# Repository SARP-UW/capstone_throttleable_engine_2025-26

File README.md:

# capstone_throttleable_engine_2025-26

2025-2026 SARP Capstone Project — a throttleable ethanol / nitrous engine injector testbed.

This repository includes:
- **software** (`software/`) — Python DAQ, valve actuation, throttle control, and web GUI
- **hardware** (`hardware/`) — KiCAD PCB design for DAQ, valve actuation, and servo control
- **analysis** (`analysis/`) — Thermal, structural, and control system analysis 

---

## Software

**Package:** `deep-thrott-code` v0.1.0  
**Requires:** Python ≥ 3.10

### Installation

```bash
pip install -e .
```

### Running the GUI

The system is split into two servers:

| Server | Default address | Role |
|--------|----------------|------|
| **Backend** | `http://0.0.0.0:6001` | DAQ, valve control, F3C sequencer, Socket.IO |
| **GUI** | `http://127.0.0.1:5000` | Serves the web frontend only |

When you open the GUI in a browser, the frontend JS automatically connects to the backend via Socket.IO on port 6001 (same host, different port). The backend streams live sensor data at ~10 Hz and receives commands (valve actuation, sequence control, start/stop logging) from the GUI.

**Running both on the same machine:**

```bash
# Terminal 1 — start the backend
python -m deep_thrott_code.main --host 0.0.0.0 --port 6001

# Terminal 2 — start the GUI server
python -m deep_thrott_code.gui.run_gui --host 0.0.0.0 --port 5000
```

Once the server is running, open any browser on the same network and navigate to:

```
http://<host-ip>:5000
```

If running locally, just go to `http://localhost:5000` or `http://127.0.0.1:5000`.  
If running on a Raspberry Pi, use the Pi's IP address: `http://192.168.x.x:5000`.

**Running backend on a Pi, GUI on your laptop:**

```bash
# On the Pi
python -m deep_thrott_code.main --host 0.0.0.0 --port 6001

# On your laptop (point GUI at the Pi's IP)
python -m deep_thrott_code.gui --backend http://192.168.x.x:6001 --host 127.0.0.1 --port 5000
```

Then open `http://localhost:5000` on your laptop.

**What you see in the browser:**

The GUI is a single-page app with:
- **Line control tabs** — PID diagrams with live valve state and pressure readouts for ethanol and nitrous lines
- **DAQ tabs** — 18 real-time sensor plots (auto-scaled, 300-point history)
- **Sequence panel** — step-by-step fire sequence tracking with manual step execution
- **Settings** — simulation toggle, test selection (hotfire / cold flow), sensor selection, theme

**CLI flags (main backend):**

| Flag | Description |
|------|-------------|
| `--host` | Bind host (default `0.0.0.0`) |
| `--port` | Bind port (default `6001`) |
| `--simulation` | Run without hardware (sensor simulation) |
| `--no-gui-server` | Start backend only, no Flask server |
| `--autostart` | Automatically start DAQ on launch |
| `--no-sequencer` | Disable the F3C fire sequencer |
| `--debug` | Enable Flask debug mode |

### Structure

```
software/src/deep_thrott_code/
├── main.py               # Entry point
├── backend/              # App factory, GUI command handlers, DAQ runtime
├── gui/                  # Flask + Socket.IO web interface (routes, sockets)
├── daq/                  # Data acquisition — ADC drivers and sensor interfaces
├── f3c/                  # Sequencer and valve control
├── control/              # PID throttle controller and servo characterization
└── config/               # Default configuration files
```

**Utility scripts** (`software/scripts/`):
- `hotfire.py` — Hotfire sequence runner
- `calibrate_sensors.py` — Sensor calibration
- `plot_daq_csv.py` — Plot data from DAQ CSV logs
- `adc_smoke_test.py` — ADC hardware smoke test

### Dependencies

| Package | Purpose |
|---------|---------|
| Flask, Flask-SocketIO | Web GUI server |
| NumPy, SciPy | Numerical computation |
| PyYAML | Configuration parsing |
| PySerial | Serial communication |
| Matplotlib | Data visualization |
| RPi.GPIO, pigpio, spidev | GPIO and SPI (Linux/RPi only) |
| eventlet *(optional)* | Async server mode |

---

## Hardware

KiCAD project located in `hardware/cda-pcb/`. Includes schematic, PCB layout, Gerber files, and custom symbols/footprints.

---

## Analysis

- `analysis/control_dev/` — Control system models (MATLAB and Python)
- `analysis/engine_dev/` — Structural analysis (Python, based on GRACE methodology)

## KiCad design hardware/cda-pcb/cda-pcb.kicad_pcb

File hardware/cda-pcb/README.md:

# High-Precision Raspberry Pi DAQ Board

A custom Data Acquisition (DAQ) hat designed for the Raspberry Pi. This board interfaces with industrial sensors (RTDs, Load Cells, Pressure Transducers) to log and display live data with high precision.

The system features a robust, low-noise power architecture that manages 24VDC input to power the sensors, the precision analog circuitry, and the Raspberry Pi itself. It utilizes dual 24-bit ADCs communicating over SPI for high-resolution signal digitization.

## Features

* **Multi-Sensor Interface:** Three 15-position D-sub connectors for attaching RTDs, Load Cells, and Pressure Transducers.
* **Input Protection:** Every signal line is protected by TVS diode arrays to guard against ESD and surge events.
* **High-Resolution Sampling:** Dual 24-bit ADCs transmit data via SPI to the Raspberry Pi.
* **Low-Noise Power Architecture:**
    * Accepts 24 VDC input.
    * On-board Buck converters for high-efficiency voltage step-down.
    * LDOs and precision voltage references ensure clean power rails for the ADCs and sensors.
    * High-current supply dedicated to the Raspberry Pi.
* **Compact Design:** PCB fits within a 10cm x 10cm footprint to minimize manufacturing costs.

### 3D Rendering

### Layout View

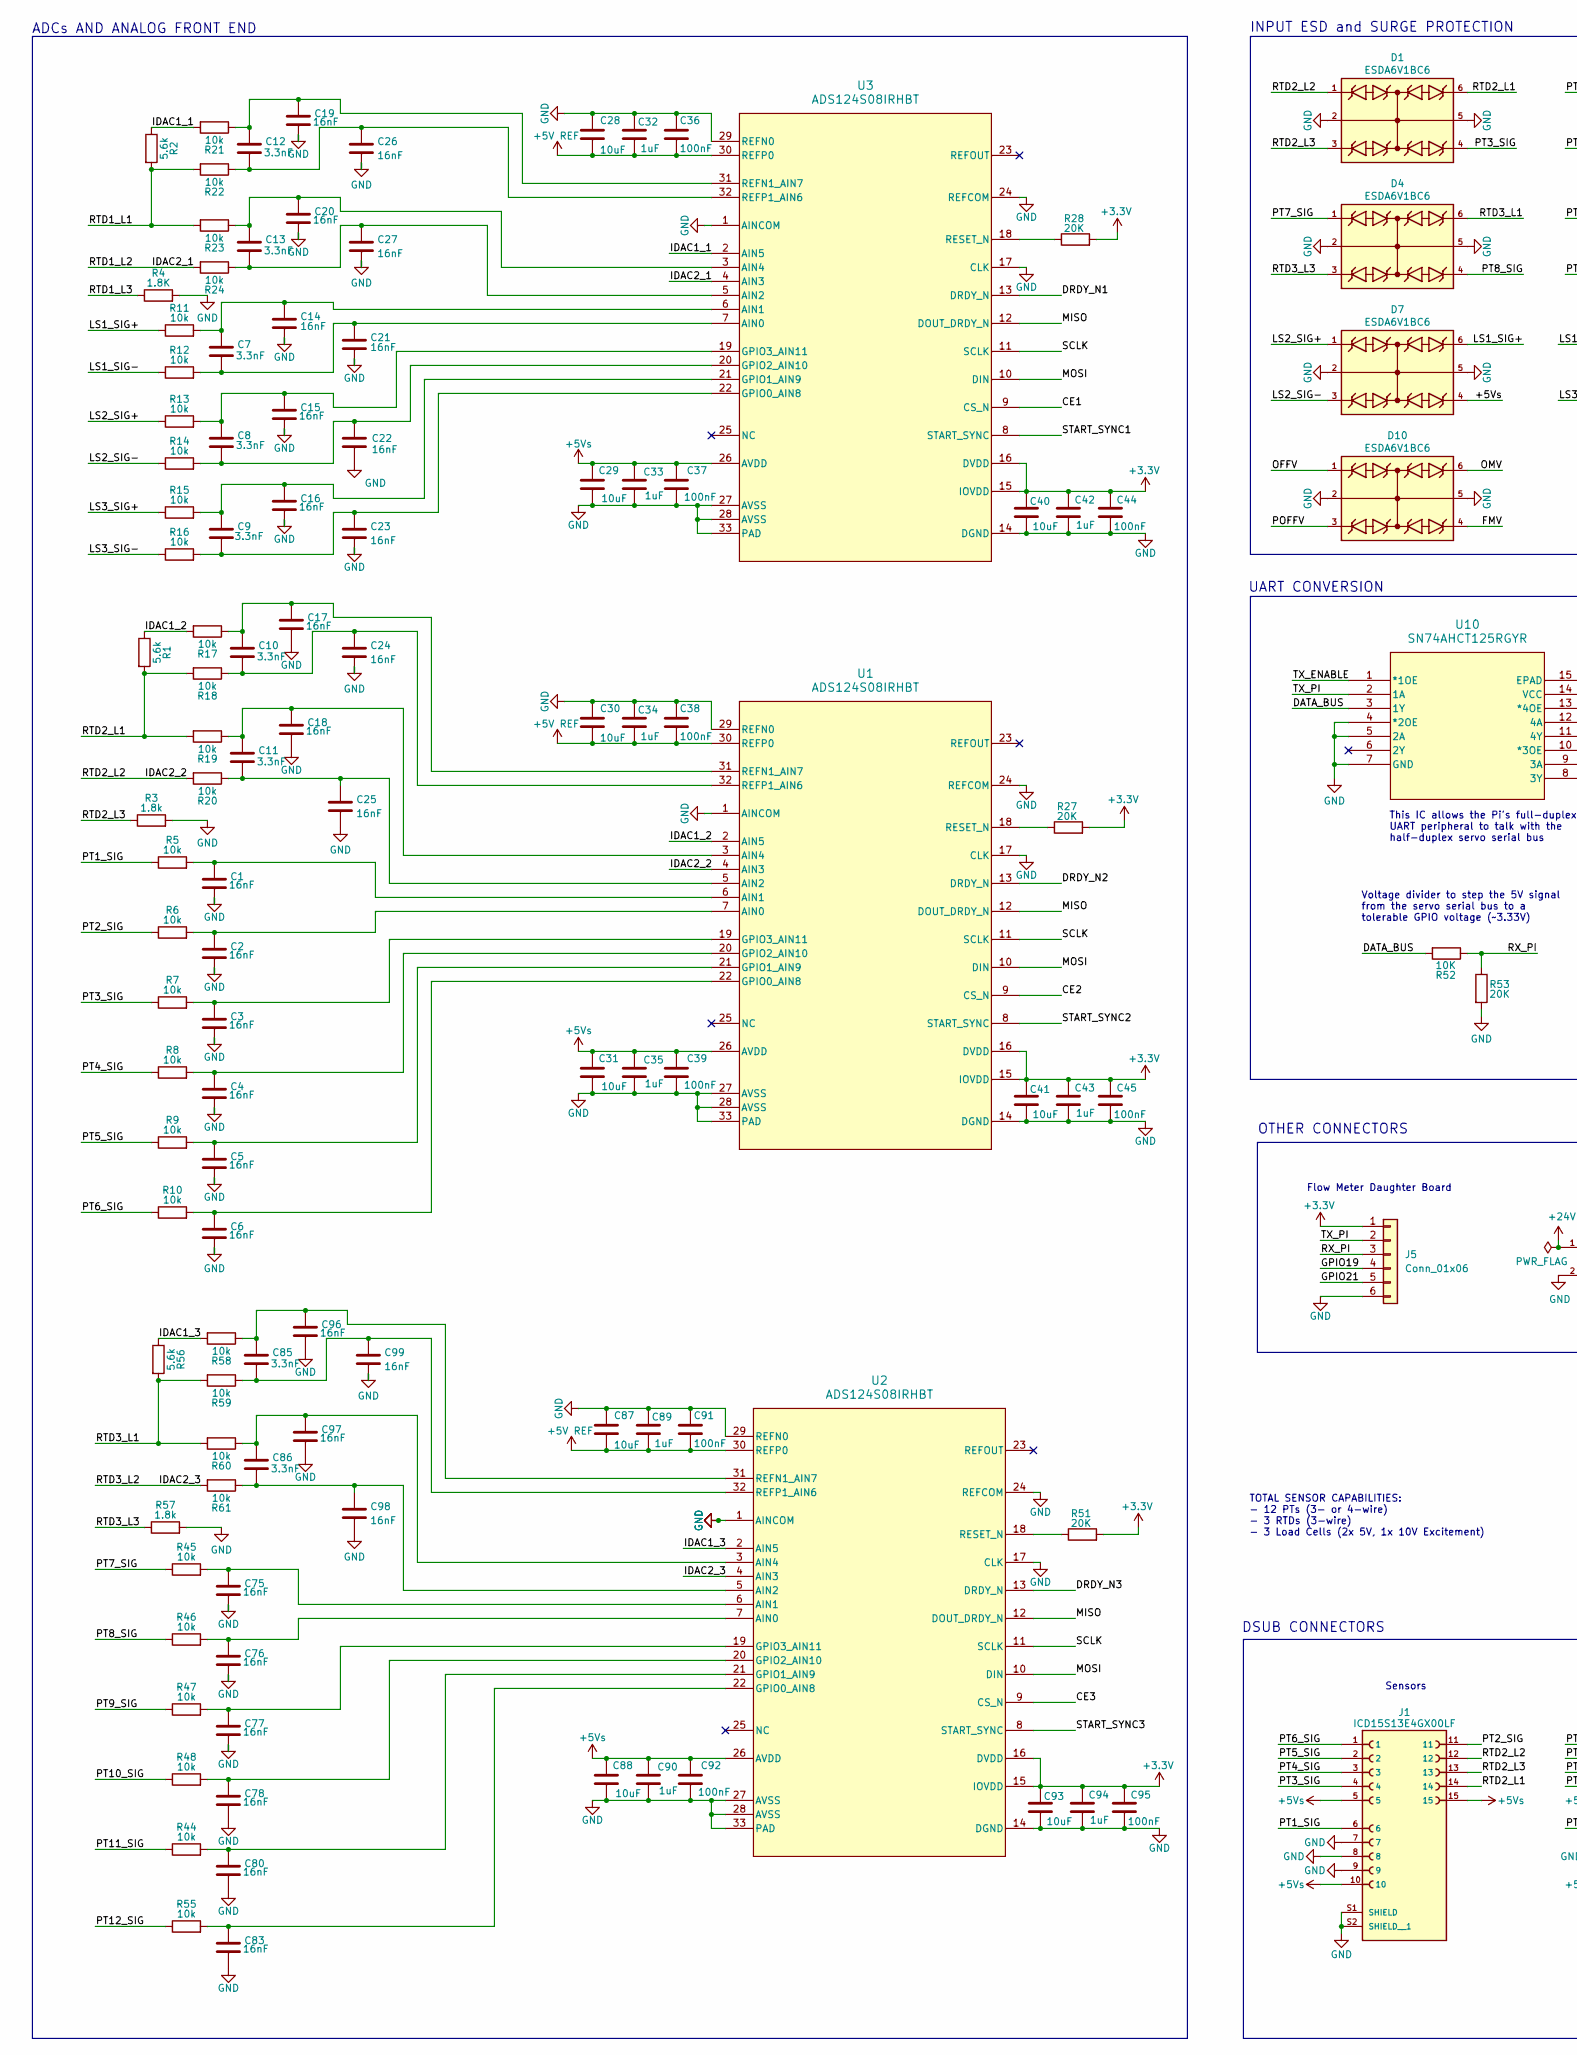
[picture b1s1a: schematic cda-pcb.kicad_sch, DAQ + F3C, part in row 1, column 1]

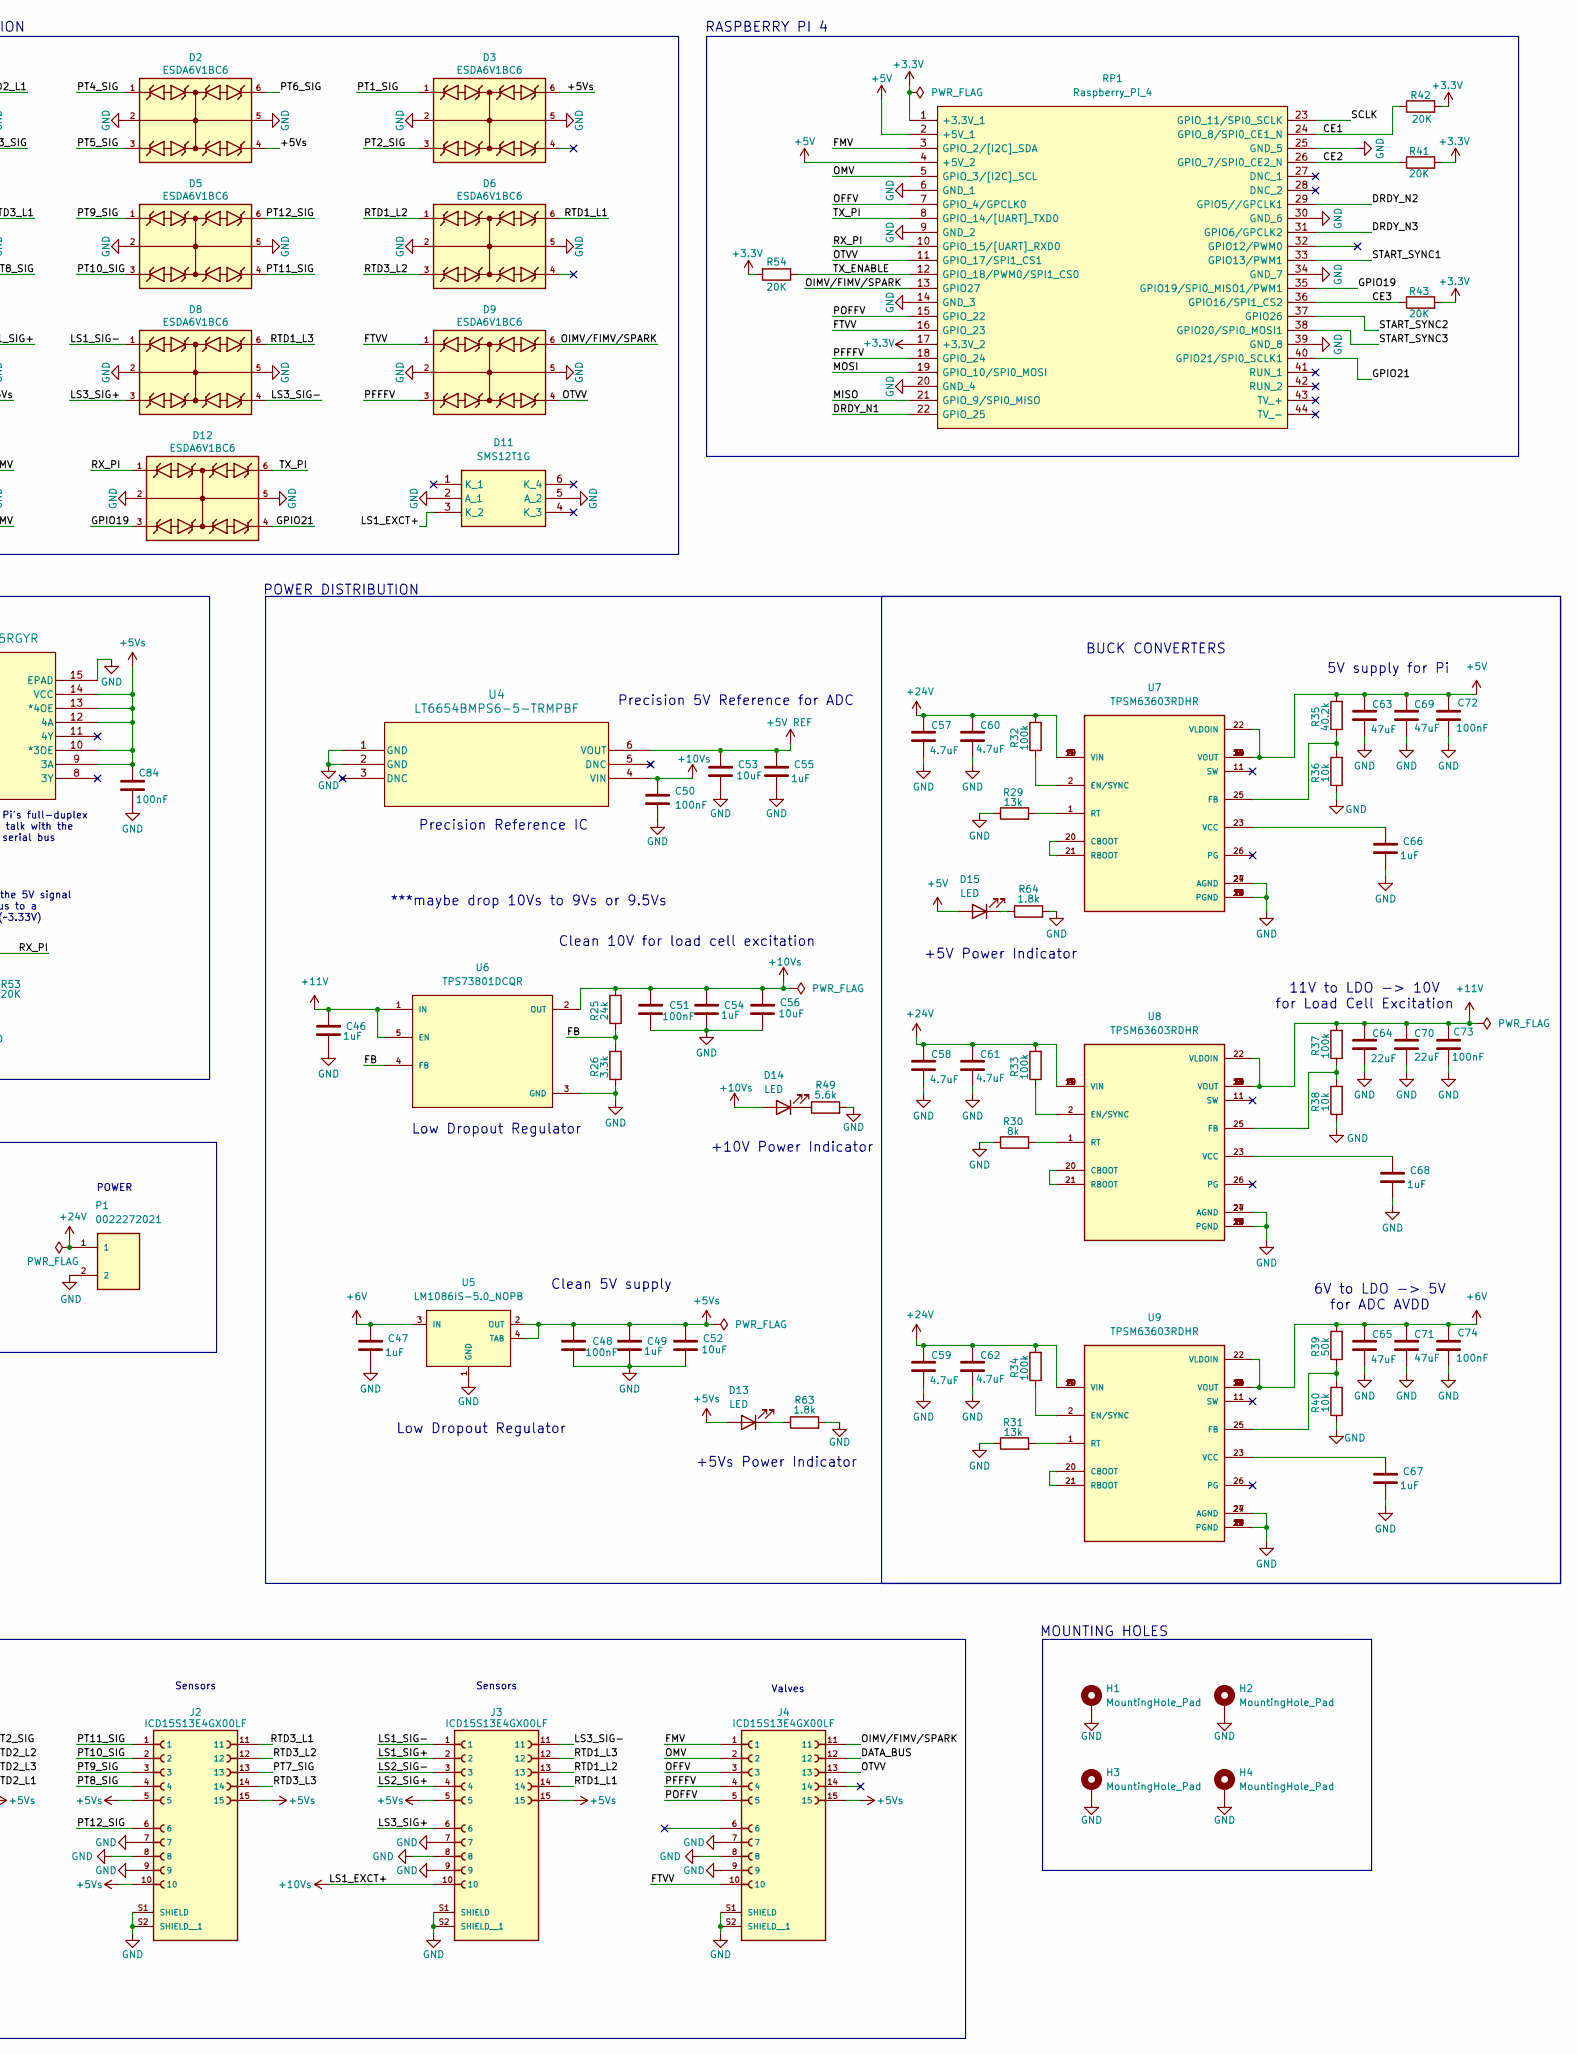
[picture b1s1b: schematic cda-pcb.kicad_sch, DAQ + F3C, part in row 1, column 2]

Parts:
C1, C2, C3, C4, C5, C6, C14, C15, C16, C17, C18, C19, C20, C21, C22, C23, C24, C25, C26, C27, C75, C76, C77, C78, C80, C83, C96, C97, C98, C99: 16nF; CAPC3216X95N
C7, C8, C9, C10, C11, C12, C13, C85, C86: 3.3nF; C_0603_1608Metric
C28, C29, C30, C31, C40, C41, C52, C53, C56, C87, C88, C93: 10uF; CAPC2012X145N
C32, C33, C34, C35, C42, C43, C46, C47, C49, C54, C55, C66, C67, C68, C89, C90, C94: 1uF; CAPC1608X94N
C36, C37, C38, C39, C44, C45, C48, C50, C51, C72, C73, C74, C84, C91, C92, C95: 100nF; CAPC1608X97N
C57, C58, C59, C60, C61, C62: 4.7uF; C_0805_2012Metric
C63, C65, C69, C71: 47uF; C_1206_3216Metric
C64, C70: 22uF; C_1206_3216Metric
D1, D2, D3, D4, D5, D6, D7, D8, D9, D10, D12: ESDA6V1BC6; SOT95P280X145-6N; PARTREV 2
D11: SMS12T1G; SOT95P275X110-6N; Manufacturer_Part_Number SMS12T1G; Mouser Part Number 863-SMS12T1G
D13, D14, D15: LED; LED_0805_2012Metric
H1, H2, H3, H4: MountingHole_Pad; MountingHole_2.5mm_Pad
J1, J2, J3, J4: ICD15S13E4GX00LF; AMPHENOL_ICD15S13E4GX00LF; PARTREV G
J5: Conn_01x06; PinHeader_1x06_P2.54mm_Vertical
P1: 0022272021; MOLEX_0022272021
R1, R2, R49, R56: 5.6k; R_0603_1608Metric
R3, R57, R63, R64: 1.8k; R_0603_1608Metric
R4: 1.8K; R_0603_1608Metric
R5, R6, R7, R8, R9, R10, R11, R12, R13, R14, R15, R16, R17, R18, R19, R20, R21, R22, R23, R24, R44, R45, R46, R47, R48, R55, R58, R59, R60, R61: 10k; R_0603_1608Metric
R25: 24k; RESC1508X50N
R26: 3.3k; RESC1508X50N
R27, R28, R41, R42, R43, R51, R53, R54: 20K; RESC1508X50N
R29, R31: 13k; RESC1508X50N
R30: 8k; RESC1508X50N
R32, R33, R34, R37: 100k; RESC1508X50N
R35: 40.2k; RESC1508X50N
R36, R38, R40: 10k; RESC1508X50N
R39: 50k; RESC1508X50N
R52: 10K; RESC1508X50N
RP1: Raspberry_Pi_4; raspberrypi_2_3; Manufacturer_Part_Number Raspberry Pi 2 or 3
U1, U2, U3: ADS124S08IRHBT; QFN50P500X500X100-33N
U4: LT6654BMPS6-5-TRMPBF; TSOT-23_S6_LIT
U5: LM1086IS-5.0_NOPB; TO254P1524X483-4N
U6: TPS73801DCQR; SOT127P706X180-6N
U7, U8, U9: TPSM63603RDHR; CONV_TPSM63602RDHR; PARTREV April 2022
U10: SN74AHCT125RGYR; RGY14_2P05X2P05

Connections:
+3.3V: C40.1, C41.1, C42.1, C43.1, C44.1, C45.1, C93.1, C94.1, C95.1, J5.1, R27.2, R28.2, R41.2, R42.2, R43.2, R51.2, R54.2, RP1.1 (+3.3V_1), RP1.17 (+3.3V_2), U1.15 (IOVDD), U1.16 (DVDD), U2.15 (IOVDD), U2.16 (DVDD), U3.15 (IOVDD), U3.16 (DVDD)
+5V: C63.2, C69.2, C72.1, D15.2 (A), R35.2, RP1.2 (+5V_1), RP1.4 (+5V_2), U7.7 (VOUT), U7.8 (VOUT), U7.9 (VOUT), U7.10 (VOUT), U7.12 (VOUT), U7.13 (VOUT), U7.14 (VOUT), U7.15 (VOUT), U7.22 (VLDOIN), U7.30 (VOUT)
+5V REF: C28.2, C30.2, C32.2, C34.2, C36.2, C38.2, C53.1, C55.1, C87.2, C89.2, C91.2, U1.30 (REFP0), U2.30 (REFP0), U3.30 (REFP0), U4.6 (VOUT)
+6V: C47.1, C65.2, C71.2, C74.1, R39.2, U5.3 (IN), U9.7 (VOUT), U9.8 (VOUT), U9.9 (VOUT), U9.10 (VOUT), U9.12 (VOUT), U9.13 (VOUT), U9.14 (VOUT), U9.15 (VOUT), U9.22 (VLDOIN), U9.30 (VOUT)
+11V: C46.1, C64.2, C70.2, C73.1, R37.2, U6.1 (IN), U6.5 (EN), U8.7 (VOUT), U8.8 (VOUT), U8.9 (VOUT), U8.10 (VOUT), U8.12 (VOUT), U8.13 (VOUT), U8.14 (VOUT), U8.15 (VOUT), U8.22 (VLDOIN), U8.30 (VOUT)
+24V: C57.2, C58.2, C59.2, C60.2, C61.2, C62.2, P1.1, R32.2, R33.2, R34.2, U7.3 (VIN), U7.4 (VIN), U7.18 (VIN), U7.19 (VIN), U8.3 (VIN), U8.4 (VIN), U8.18 (VIN), U8.19 (VIN), U9.3 (VIN), U9.4 (VIN), U9.18 (VIN), U9.19 (VIN)
/CE1: R42.1, RP1.24 (GPIO_8/SPI0_CE1_N), U3.9 (CS_N)
/CE2: R41.1, RP1.26 (GPIO_7/SPI0_CE2_N), U1.9 (CS_N)
/CE3: R43.1, RP1.36 (GPIO16/SPI1_CS2), U2.9 (CS_N)
/DATA_BUS: J4.12, R52.2, U10.3 (1Y)
/DRDY_N1: RP1.22 (GPIO_25), U3.13 (DRDY_N)
/DRDY_N2: RP1.29 (GPIO5//GPCLK1), U1.13 (DRDY_N)
/DRDY_N3: RP1.31 (GPIO6/GPCLK2), U2.13 (DRDY_N)
/FB: R25.1, R26.2, U6.4 (FB)
/FMV: D10.4, J4.1, RP1.3 (GPIO_2/[I2C]_SDA)
/FTVV: D9.1, J4.10, RP1.16 (GPIO_23)
/GPIO19: D12.3, J5.4, RP1.35 (GPIO19/SPI0_MISO1/PWM1)
/GPIO21: D12.4, J5.5, RP1.40 (GPIO21/SPI0_SCLK1)
/IDAC1_1: R2.1, R21.2, U3.2 (AIN5)
/IDAC1_2: R1.1, R17.2, U1.2 (AIN5)
/IDAC1_3: R56.1, R58.2, U2.2 (AIN5)
/IDAC2_1: D6.1, J3.13, R24.2, U3.4 (AIN3)
/IDAC2_2: D1.1, J1.12, R20.2, U1.4 (AIN3)
/IDAC2_3: D6.3, J2.12, R61.2, U2.4 (AIN3)
/LS1_SIG+: D7.6, J3.2, R11.1
/LS1_SIG-: D8.1, J3.1, R12.1
/LS2_SIG+: D7.1, J3.4, R13.1
/LS2_SIG-: D7.3, J3.3, R14.1
/LS3_SIG+: D8.3, J3.6, R15.1
/LS3_SIG-: D8.4, J3.11, R16.1
/MISO: RP1.21 (GPIO_9/SPI0_MISO), U1.12 (DOUT_DRDY_N), U2.12 (DOUT_DRDY_N), U3.12 (DOUT_DRDY_N)
/MOSI: RP1.19 (GPIO_10/SPI0_MOSI), U1.10 (DIN), U2.10 (DIN), U3.10 (DIN)
/OFFV: D10.1, J4.3, RP1.7 (GPIO_4/GPCLK0)
/OIMV/FIMV/SPARK: D9.6, J4.11, RP1.13 (GPIO27)
/OMV: D10.6, J4.2, RP1.5 (GPIO_3/[I2C]_SCL)
/OTVV: D9.4, J4.13, RP1.11 (GPIO_17/SPI1_CS1)
/PFFFV: D9.3, J4.4, RP1.18 (GPIO_24)
/POFFV: D10.3, J4.5, RP1.15 (GPIO_22)
/PT1_SIG: D3.1, J1.6, R5.1
/PT2_SIG: D3.3, J1.11, R6.1
/PT3_SIG: D1.4, J1.4, R7.1
/PT4_SIG: D2.1, J1.3, R8.1
/PT5_SIG: D2.3, J1.2, R9.1
/PT6_SIG: D2.6, J1.1, R10.1
/PT7_SIG: D4.1, J2.13, R45.1
/PT8_SIG: D4.4, J2.4, R46.1
/PT9_SIG: D5.1, J2.3, R47.1
/PT10_SIG: D5.3, J2.2, R48.1
/PT11_SIG: D5.4, J2.1, R44.1
/PT12_SIG: D5.6, J2.6, R55.1
/RTD1_L1: D6.6, J3.14, R2.2, R22.2, R23.2
/RTD1_L3: D8.6, J3.12, R4.1
/RTD2_L1: D1.6, J1.14, R1.2, R18.2, R19.2
/RTD2_L3: D1.3, J1.13, R3.1
/RTD3_L1: D4.6, J2.11, R56.2, R59.2, R60.2
/RTD3_L3: D4.3, J2.14, R57.1
/RX_PI: D12.1, J5.3, R52.1, R53.1, RP1.10 (GPIO_15/[UART]_RXD0)
/SCLK: RP1.23 (GPIO_11/SPI0_SCLK), U1.11 (SCLK), U2.11 (SCLK), U3.11 (SCLK)
/START_SYNC1: RP1.33 (GPIO13/PWM1), U3.8 (START_SYNC)
/START_SYNC2: RP1.37 (GPIO26), U1.8 (START_SYNC)
/START_SYNC3: RP1.38 (GPIO20/SPI0_MOSI1), U2.8 (START_SYNC)
/TX_ENABLE: R54.1, RP1.12 (GPIO_18/PWM0/SPI1_CS0), U10.1 (*1OE)
/TX_PI: D12.6, J5.2, RP1.8 (GPIO_14/[UART]_TXD0), U10.2 (1A)
GND: C1.2, C2.2, C3.2, C4.2, C5.2, C6.2, C14.2, C15.2, C16.2, C17.2, C18.2, C19.2, C20.2, C21.2, C22.2, C23.2, C24.2, C25.2, C26.2, C27.2, C28.1, C29.2, C30.1, C31.2, C32.1, C33.2, C34.1, C35.2, C36.1, C37.2, C38.1, C39.2, C40.2, C41.2, C42.2, C43.2, C44.2, C45.2, C46.2, C47.2, C48.2, C49.2, C50.2, C51.2, C52.2, C53.2, C54.2, C55.2, C56.2, C57.1, C58.1, C59.1, C60.1, C61.1, C62.1, C63.1, C64.1, C65.1, C66.2, C67.2, C68.2, C69.1, C70.1, C71.1, C72.2, C73.2, C74.2, C75.2, C76.2, C77.2, C78.2, C80.2, C83.2, C84.2, C87.1, C88.2, C89.1, C90.2, C91.1, C92.2, C93.2, C94.2, C95.2, C96.2, C97.2, C98.2, C99.2, D1.2, D1.5, D2.2, D2.5, D3.2, D3.5, D4.2, D4.5, D5.2, D5.5, D6.2, D6.5, D7.2, D7.5, D8.2, D8.5, D9.2, D9.5, D10.2, D10.5, D11.2 (A_1), D11.5 (A_2), D12.2, D12.5, H1.1, H2.1, H3.1, H4.1, J1.7, J1.8, J1.9, J1.S1 (SHIELD), J1.S2 (SHIELD__1), J2.7, J2.8, J2.9, J2.S1 (SHIELD), J2.S2 (SHIELD__1), J3.7, J3.8, J3.9, J3.S1 (SHIELD), J3.S2 (SHIELD__1), J4.7, J4.8, J4.9, J4.S1 (SHIELD), J4.S2 (SHIELD__1), J5.6, P1.2, R3.2, R4.2, R26.1, R29.1, R30.1, R31.1, R36.1, R38.1, R40.1, R49.2, R53.2, R57.2, R63.2, R64.2, RP1.6 (GND_1), RP1.9 (GND_2), RP1.14 (GND_3), RP1.20 (GND_4), RP1.25 (GND_5), RP1.30 (GND_6), RP1.34 (GND_7), RP1.39 (GND_8), U1.1 (AINCOM), U1.14 (DGND), U1.17 (CLK), U1.24 (REFCOM), U1.27 (AVSS), U1.28 (AVSS), U1.29 (REFN0), U1.33 (PAD), U2.1 (AINCOM), U2.14 (DGND), U2.17 (CLK), U2.24 (REFCOM), U2.27 (AVSS), U2.28 (AVSS), U2.29 (REFN0), U2.33 (PAD), U3.1 (AINCOM), U3.14 (DGND), U3.17 (CLK), U3.24 (REFCOM), U3.27 (AVSS), U3.28 (AVSS), U3.29 (REFN0), U3.33 (PAD), U4.1 (GND), U4.2 (GND), U5.1 (GND), U6.3 (GND), U7.5 (PGND), U7.6 (PGND), U7.16 (PGND), U7.17 (PGND), U7.24 (AGND), U7.27 (AGND), U7.28 (PGND), U7.29 (PGND), U8.5 (PGND), U8.6 (PGND), U8.16 (PGND), U8.17 (PGND), U8.24 (AGND), U8.27 (AGND), U8.28 (PGND), U8.29 (PGND), U9.5 (PGND), U9.6 (PGND), U9.16 (PGND), U9.17 (PGND), U9.24 (AGND), U9.27 (AGND), U9.28 (PGND), U9.29 (PGND), U10.4 (*2OE), U10.5 (2A), U10.7 (GND), U10.15 (EPAD)
unnamed: D13.1 (K), R63.1
unnamed: D14.1 (K), R49.1
unnamed: D15.1 (K), R64.1
unnamed: C2.1, R6.2, U1.7 (AIN0)
unnamed: C1.1, R5.2, U1.6 (AIN1)
unnamed: C11.2, C25.1, R20.1, U1.5 (AIN2)
unnamed: C11.1, C18.1, R19.1, U1.3 (AIN4)
unnamed: C6.1, R10.2, U1.22 (GPIO0_AIN8)
unnamed: C5.1, R9.2, U1.21 (GPIO1_AIN9)
unnamed: C4.1, R8.2, U1.20 (GPIO2_AIN10)
unnamed: C3.1, R7.2, U1.19 (GPIO3_AIN11)
unnamed: C10.1, C17.1, R17.1, U1.31 (REFN1_AIN7)
unnamed: C10.2, C24.1, R18.1, U1.32 (REFP1_AIN6)
unnamed: R27.1, U1.18 (RESET_N)
unnamed: C76.1, R46.2, U2.7 (AIN0)
unnamed: C75.1, R45.2, U2.6 (AIN1)
unnamed: C86.2, C98.1, R61.1, U2.5 (AIN2)
unnamed: C86.1, C97.1, R60.1, U2.3 (AIN4)
unnamed: C83.1, R55.2, U2.22 (GPIO0_AIN8)
unnamed: C80.1, R44.2, U2.21 (GPIO1_AIN9)
unnamed: C78.1, R48.2, U2.20 (GPIO2_AIN10)
unnamed: C77.1, R47.2, U2.19 (GPIO3_AIN11)
unnamed: C85.1, C96.1, R58.1, U2.31 (REFN1_AIN7)
unnamed: C85.2, C99.1, R59.1, U2.32 (REFP1_AIN6)
unnamed: R51.1, U2.18 (RESET_N)
unnamed: C7.2, C21.1, R12.2, U3.7 (AIN0)
unnamed: C7.1, C14.1, R11.2, U3.6 (AIN1)
unnamed: C13.2, C27.1, R24.1, U3.5 (AIN2)
unnamed: C13.1, C20.1, R23.1, U3.3 (AIN4)
unnamed: C9.2, C23.1, R16.2, U3.22 (GPIO0_AIN8)
unnamed: C9.1, C16.1, R15.2, U3.21 (GPIO1_AIN9)
unnamed: C8.2, C22.1, R14.2, U3.20 (GPIO2_AIN10)
unnamed: C8.1, C15.1, R13.2, U3.19 (GPIO3_AIN11)
unnamed: C12.1, C19.1, R21.1, U3.31 (REFN1_AIN7)
unnamed: C12.2, C26.1, R22.1, U3.32 (REFP1_AIN6)
unnamed: R28.1, U3.18 (RESET_N)
unnamed: U7.20 (CBOOT), U7.21 (RBOOT)
unnamed: R32.1, U7.2 (EN/SYNC)
unnamed: R35.1, R36.2, U7.25 (FB)
unnamed: R29.2, U7.1 (RT)
unnamed: C66.1, U7.23 (VCC)
unnamed: U8.20 (CBOOT), U8.21 (RBOOT)
unnamed: R33.1, U8.2 (EN/SYNC)
unnamed: R37.1, R38.2, U8.25 (FB)
unnamed: R30.2, U8.1 (RT)
unnamed: C68.1, U8.23 (VCC)
unnamed: U9.20 (CBOOT), U9.21 (RBOOT)
unnamed: R34.1, U9.2 (EN/SYNC)
unnamed: R39.1, R40.2, U9.25 (FB)
unnamed: R31.2, U9.1 (RT)
unnamed: C67.1, U9.23 (VCC)

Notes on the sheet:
Sensors
RASPBERRY PI 4
Low Dropout Regulator
5V supply for Pi
This IC allows the Pi's full-duplex UART peripheral to talk with the half-duplex servo serial bus
Valves
***maybe drop 10Vs to 9Vs or 9.5Vs
Flow Meter Daughter Board
+5Vs Power Indicator
6V to LDO -> 5V for ADC AVDD
BUCK CONVERTERS
MOUNTING HOLES
Clean 5V supply
Clean 10V for load cell excitation
INPUT ESD and SURGE PROTECTION
11V to LDO -> 10V for Load Cell Excitation
+5V Power Indicator
OTHER CONNECTORS
POWER DISTRIBUTION
TOTAL SENSOR CAPABILITIES: - 12 PTs (3- or 4-wire) - 3 RTDs (3-wire) - 3 Load Cells (2x 5V, 1x 10V Excitement)
POWER
Voltage divider to step the 5V signal from the servo serial bus to a tolerable GPIO voltage (~3.33V)
+10V Power Indicator
ADCs AND ANALOG FRONT END
DSUB CONNECTORS
Precision Reference IC
Precision 5V Reference for ADC
UART CONVERSION

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
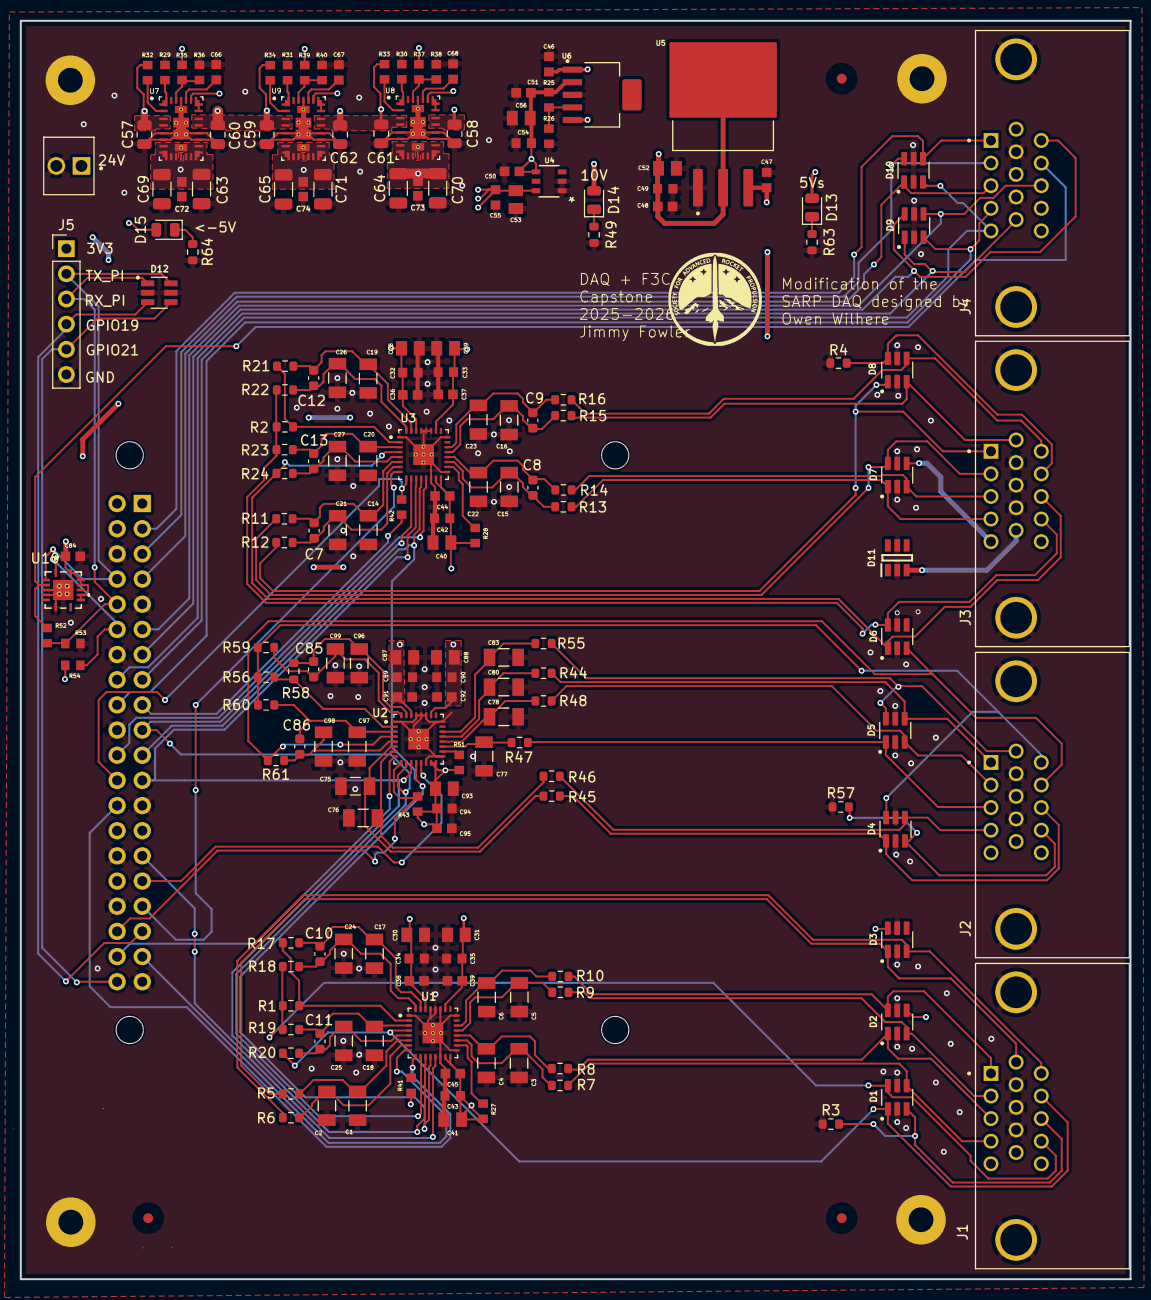
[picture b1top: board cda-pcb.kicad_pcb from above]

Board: 4 copper layers, 112.0 x 127.0 mm, 194 parts (1 on the bottom side), 117 nets.

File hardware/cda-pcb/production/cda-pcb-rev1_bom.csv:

Designator,Footprint,Quantity,Value,LCSC Part #
"C1, C14, C15, C16, C17, C18, C19, C2, C20, C21, C22, C23, C24, C25, C26, C27, C3, C4, C5, C6, C75, C76, C77, C78, C80, C83, C96, C97, C98, C99",CAPC3216X95N,30,16nF,
"C10, C11, C12, C13, C7, C8, C85, C86, C9",0603,9,3.3nF,
"C28, C29, C30, C31, C40, C41, C52, C53, C56, C87, C88, C93",CAPC2012X145N,12,10uF,
"C32, C33, C34, C35, C42, C43, C46, C47, C49, C54, C55, C66, C67, C68, C89, C90, C94",CAPC1608X94N,17,1uF,
"C36, C37, C38, C39, C44, C45, C48, C50, C51, C72, C73, C74, C84, C91, C92, C95",CAPC1608X97N,16,100nF,
"C57, C58, C59, C60, C61, C62",0805,6,4.7uF,
"C63, C65, C69, C71",1206,4,47uF,
"C64, C70",1206,2,22uF,
"D1, D10, D2, D3, D4, D5, D6, D7, D8, D9",SOT95P280X145-6N,10,ESDA6V1BC6,
D11,SOT95P275X110-6N,1,SMS12T1G,
"H1, H2, H3, H4",MountingHole_2.5mm_Pad,4,MountingHole_Pad,
"J1, J2, J3, J4",AMPHENOL_ICD15S13E4GX00LF,4,ICD15S13E4GX00LF,
J6,PinHeader_1x06_P2.54mm_Vertical,1,Conn_01x06,
P1,MOLEX_0022272021,1,0022272021,
"R1, R2, R56",0603,3,5.6k,
"R10, R11, R12, R13, R14, R15, R16, R17, R18, R19, R20, R21, R22, R23, R24, R44, R45, R46, R47, R48, R5, R55, R58, R59, R6, R60, R61, R7, R8, R9",0603,30,10k,
R25,RESC1508X50N,1,24k,
R26,RESC1508X50N,1,3.3k,
"R27, R28, R41, R42, R43, R51, R53, R54",RESC1508X50N,8,20K,
"R29, R31",RESC1508X50N,2,13k,
"R3, R4, R57",0603,3,1.8k,
R30,RESC1508X50N,1,8k,
"R32, R33, R34, R37",RESC1508X50N,4,100k,
R35,RESC1508X50N,1,40.2k,
"R36, R38, R40, R52",RESC1508X50N,4,10k,
R39,RESC1508X50N,1,50k,
RP1,raspberrypi_2_3,1,Raspberry_Pi_4,
"U1, U2",QFN50P500X500X100-33N,2,ADS124S08IRHBT,
U10,RGY14_2P05X2P05,1,SN74AHCT125RGYR,
U3,RHB0032M,1,ADS124S08IRHBT,
U4,TSOT-23_S6_LIT,1,LT6654BMPS6-5-TRMPBF,
U5,TO254P1524X483-4N,1,LM1086IS-5.0_NOPB,
U6,SOT127P706X180-6N,1,TPS73801DCQR,
"U7, U8, U9",CONV_TPSM63602RDHR,3,TPSM63603RDHR,

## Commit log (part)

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2026-05-20 load cell configs
2026-05-21 load cell config change
2026-05-21 drdy gpio change for adc1
2026-05-21 DRDY1 REVERT
2026-05-21 smoke test edits
2026-05-21 updated with throttle valves
2026-05-21 make logger general for valve actuation
2026-05-21 change to pigpio, add logger, add comments
2026-05-21 read response echo robust fix
2026-05-21 instagram reels
2026-05-21 update throttle valve initialization
2026-05-21 pulsing
2026-05-21 logger changes
2026-05-21 uncomment read pos
2026-05-21 changed checksum_found to variable instead of field
2026-05-21 get rid of condition valves, fix fill
2026-05-21 date + time
2026-05-21 add valve id initialization
2026-05-21 valve id assignment debugging
2026-05-21 debugging
2026-05-21 add back read servo id
2026-05-21 comment out valve_id assignment
2026-05-21 echo debugging again
2026-05-21 add echo debugging prints
2026-05-21 sleep in echo drain loop
2026-05-21 more echo debugging
2026-05-21 up sampling rate
2026-05-21 moving throttle valves to fill
2026-05-21 trying to throttle two valves
2026-05-21 adding throttle open loop functionality
2026-05-21 making actuation time a variable in set_state
2026-05-21 sampling rate fix
2026-05-21 updates for f3c checkout
2026-05-21 edits
2026-05-22 route fix
2026-05-22 adc fix
2026-05-22 adc smoke test edits
2026-05-22 switching back
2026-05-22 temp adc spi device switch
2026-05-22 gpio cs for adc1
2026-05-22 switch back
2026-05-22 streaming
2026-05-22 load cell voltage streaming
2026-05-22 new adc configs
2026-05-22 manual cs test program
2026-05-22 corrected gpio on test program
2026-05-22 gpio number fix
2026-05-22 cs fix to adc class + initialization in sensors
2026-05-22 manual gpio switches for smoke test
2026-05-22 added gpio num
2026-05-22 load cell specs
2026-05-22 pin conflicts
2026-05-22 dropping sample fix
2026-05-22 logging files
2026-05-22 dropping sample fix again
2026-05-22 closing fix
2026-05-22 closing fix again
2026-05-22 dropped samples print
2026-05-22 lock change
2026-05-22 load cell gains
2026-05-23 implement f3c logging
2026-05-23 commenting controller and sequences
2026-05-23 uncomment read_pos, only command valve_id 2
2026-05-23 add computer_sim to valve.py
2026-05-23 pigpio computer_sim functionality
2026-05-23 f3c test log 1
2026-05-23 comment reads
2026-05-23 added open loop throttle
2026-05-23 relay test
2026-05-23 added sleeps for relay test
2026-05-23 f3c main debug log
2026-05-23 flush every valve actuation
2026-05-23 logger debugging log
2026-05-23 computer_sim = false
2026-05-23 relay test pin numbering + misc fixes
2026-05-23 logger import statement debug
2026-05-23 turn on off loop
2026-05-23 import fix
2026-05-23 update throttle steps
2026-05-23 set up two logger implementation
2026-05-23 resolve logger conflicts
2026-05-23 pigpio debugging
2026-05-23 import
2026-05-24 removed uart_pigpio_test script
2026-05-24 logging
2026-05-24 logger debugs
2026-05-24 time fix
2026-05-24 renamed cores for zero indexing
2026-05-24 gui fixes
2026-05-24 colors
2026-05-24 gui changes
2026-05-24 pid tab fix
2026-05-24 uncomment servo id assignment
2026-05-24 changing flush
2026-05-24 controller.py logger updates
2026-05-24 adding state field to throttle valve
2026-05-24 valve id assignment change
2026-05-24 added test valve actuation
2026-05-24 pid pictures
2026-05-24 html changes again
2026-05-24 more html changes
2026-05-24 pid stage expand
2026-05-24 pid shrink issue
2026-05-24 pid shrink issue trying to fix
2026-05-24 moved buttons
2026-05-25 computer sim update
2026-05-25 return to nominal
2026-05-25 small gui valve edits
2026-05-25 more gui updates
2026-05-25 refrehs error and daq button height change
2026-05-25 more fixes
2026-05-25 crash fix
2026-05-25 panel width and gap width changes
2026-05-25 updating sequences/hardware
2026-05-25 throttle valve action = None
2026-05-25 servo normal state
2026-05-25 servo actuation update
2026-05-25 comment out of valve id assignment
2026-05-25 adding nc attribute
2026-05-25 rtd configs
2026-05-25 changed chirp to decent servo
2026-05-25 added normally_closed arg to chirp test
2026-05-25 using broadcasting ID 254
2026-05-25 commented id request
2026-05-25 remade throttle command to test
2026-05-25 added comments
2026-05-25 pqoijfqpkvdijqnjbv
2026-05-25 modified throttle func
2026-05-25 THIS ONE MADE THE SERVO DO THE THING
2026-05-25 changed LS3 to FM1 and FM2
2026-05-25 flow meter + button fix
2026-05-25 daq grid
2026-05-25 axis changes
2026-05-25 cc-pt patch
2026-05-25 live samplign rate stats
2026-05-25 producer sampling rate fix
2026-05-25 scheduler fix
2026-05-25 cache fix
2026-05-25 disabled slower sensors
2026-05-25 up multiplier
2026-05-25 disabled drdy wait time
2026-05-25 emit producer/consumer stats
2026-05-25 monitor enabled
2026-05-25 implemented WaterValvePWM class
2026-05-25 deleted drdy sleep
2026-05-25 threading fix
2026-05-25 skdjfh
2026-05-25 TESTING
2026-05-25 spi clock
2026-05-25 lijsdfl
2026-05-25 testing water valves
2026-05-25 stop/start command fix
2026-05-25 settle discard disabled
2026-05-25 enable sensor
2026-05-26 drdy edge wait change
2026-05-26 switch back multiplier
2026-05-26 drdy change reverted + increased multiplier
2026-05-26 sampling rate changes
2026-05-26 disabled some slow sensors again to compare noise
2026-05-26 settle discard true
2026-05-26 enable all sensors
2026-05-26 adc sampling order change
2026-05-26 enable / sampling rate change
2026-05-26 enabled everything but rtds
2026-05-26 rtd fix
2026-05-26 rtds enabled
2026-05-26 transition settle rtd
2026-05-26 pwm valve update
    Added
2026-05-26 pwm valve update
2026-05-26 f3c import debug
2026-05-26 noisy rtds
2026-05-26 rtd config
2026-05-26 rtd current change
2026-05-26 finalize pin numbering
2026-05-26 cleaning
2026-05-26 ftfv and otfv tie together
2026-05-26 added is_normally_closed for pwm
2026-05-26 added get_valve_id to other valves
2026-05-26 pulse debugging
2026-05-26 pulse button
2026-05-26 gui freeze
2026-05-26 igniter valve config
2026-05-26 get_state for pwm
2026-05-26 igniter valve fixes
2026-05-26 added get_state to throttle valve
2026-05-26 disabled everything but adc3
2026-05-26 disabled more stuffs
2026-05-26 disabled rtds
2026-05-26 more attempts to fix RTDs
2026-05-26 enabled rtds
2026-05-26 rtd register fixes
2026-05-26 sensors zeroing stuffs
2026-05-26 throttle sva debugging prints
2026-05-26 set_state in servo_chirp.py
2026-05-26 remove _
2026-05-26 pigpio fix
2026-05-26 more rtd fixes
2026-05-26 pigpio in pwm
2026-05-26 serial_handle print
2026-05-26 added pi arg to pwm
2026-05-26 rtd fix again
2026-05-26 main shutdown + more rtd fix
2026-05-26 pwm arg fix
2026-05-26 rtd debug statements
2026-05-26 bruh
2026-05-26 debugging servos
2026-05-26 fix pwm import
2026-05-26 fix pwm args
2026-05-26 fix throttle servo args
2026-05-26 print debugging statements
2026-05-26 rtd reg readback print
2026-05-26 uart id broadcast
2026-05-26 valve iding
2026-05-26 rtd tests
2026-05-26 set actuation time to 0 in set_state
2026-05-26 move manual step wait to before actuation
2026-05-26 change pwm actuation in sequences
2026-05-27 fixing state updates in sequence
2026-05-27 coldflow throttle updates
2026-05-27 fm test
2026-05-27 zero change
2026-05-27 fm configs + deleted debug prints
2026-05-27 plot daq csv reads most recent csv
2026-05-28 error fix
2026-05-28 pt numbers change
2026-05-28 change f3c log filepath
2026-05-28 gui layout colors
2026-05-28 sensor config enable
2026-05-28 baja blast
2026-05-28 baja blast mode
2026-05-28 load cell conversion
2026-05-29 dependencies toml
2026-05-29 toml rename
2026-05-29 small color change
2026-05-29 color changes
2026-05-29 text color change
2026-05-29 tab colors
2026-05-29 edited servo_chirp to check throttle valves
2026-05-29 water test config
2026-05-29 conversions flow meter
2026-05-29 mod servo chirp inputs
2026-05-29 flow meter conversions
2026-05-29 flow meter water test
2026-05-29 gui colors updates?
2026-05-29 added prints
2026-05-29 pause for 10sec
2026-05-29 just pulling tx enable high and low
2026-05-29 changing tx_enable to gpio20
2026-05-30 rtd testing config + flow meter data analysis
2026-05-30 rtd software conversions changes
2026-05-30 bunch of gui updates
2026-05-30 sensor enabled by default, gui visual changes
2026-05-30 sensor config change
2026-05-30 reels button change
2026-05-30 rtd class change function call
2026-05-30 new uart_test
2026-05-30 wodhfwlefijwljkdnlv
2026-05-30 added second sleep
2026-05-30 tx_enable = 18
2026-05-30 adding prints)
2026-05-30 changed TX_ENABLE_PIN to 20
2026-05-30 CHANGING TX_ENABLE_PIN to 20 IN VALVE.py ALSO
2026-05-30 unhardcode tx_enable_pin
2026-05-30 pass tx_enable_pin into throttlevalve
2026-06-01 coldflow sequence throttle steps
2026-06-01 throttle calibration
2026-06-01 coldflow sequence
2026-06-01 Revert "throttle calibration"
    This reverts commit 1dcbe17287cd1101a11d33deecc6e0f047c13ac3.
2026-06-01 Revert "coldflow sequence throttle steps"
    This reverts commit abe15b03e85f8c94de44c110afdfde07a9664a84.
2026-06-01 Revert "pass tx_enable_pin into throttlevalve"
    This reverts commit 5317354fd0e7837093d4608796a20e48c0210dfb.
2026-06-01 Reapply "coldflow sequence throttle steps"
    This reverts commit e5e59b072ab9cc5fa9cf711bc920824abcc58827.
2026-06-01 Revert "unhardcode tx_enable_pin"
    This reverts commit ea7cef960d10b26dfe56329034ef71d317f5e337.
2026-06-01 Revert "Reapply "throttle calibration""
    This reverts commit bec56f1b42413d15a2f0bcf2559fcf8e9655842c.
2026-06-01 Revert "Reapply "coldflow sequence throttle steps""
    This reverts commit 8a42bccd5f199753e4f32f1cd5f13b9e9f53d689.
2026-06-01 throttle calibration 2
2026-06-01 throttle calibration 3 omctv
2026-06-01 fmctv calibration
2026-06-01 fmctv calib
2026-06-01 fmctv calib 2
2026-06-01 fmctv calib again
2026-06-01 made script for setting water valve angle
2026-06-01 updated water PWM servo to 45deg open 135deg close
2026-06-01 cpu debugging
2026-06-01 unit conversion to lbs
2026-06-01 gui background emitter now starts only when socketio client connects
2026-06-01 rtds disabled
2026-06-01 rtd debugging stuff deleted
2026-06-01 server diagnostics
2026-06-01 wrong server mode patch
2026-06-01 socket patches
2026-06-01 init import fixes
2026-06-01 eventlet revert
2026-06-01 simple websocket patch
2026-06-01 cache patch
2026-06-01 pt conversions update
2026-06-01 throttle angle calibration adjustment
2026-06-01 load cell rating updates
2026-06-02 servo angle fix
2026-06-02 servos normally open -> normally closed
2026-06-02 load cell configs + controller changes
2026-06-02 PT 6 and 7 swap, xf-pt range update
2026-06-03 removed ftfv
2026-06-03 p&id with main pt moved
2026-06-03 moved buttons after p&id changes
2026-06-03 accidentally swapped to ccpt last commit
2026-06-03 throttle steps for cold flow
2026-06-03 omctv angle calib fix
2026-06-03 omctv calib fix
2026-06-03 omctv calib
2026-06-03 throttle valve calib
2026-06-04 made script for aligning uart servos
2026-06-04 cold flow fill sequence update
2026-06-04 flow meter enabled
2026-06-04 flow meter calibration added into consumer loop
2026-06-04 ft pt calibration
2026-06-05 fixed print statement
2026-06-05 throttle time set to 0.0
2026-06-05 add otfv to sequence
2026-06-05 new of pt calibration + cold flow data analysis
2026-06-06 igniter test sequence
2026-06-08 cold flow data analysis
2026-06-09 fire sequence change and cold flow data analysis updates
2026-06-10 update reynolds num calc
2026-06-10 readme update
2026-06-10 readme slight update
2026-06-10 readme
2026-06-10 cleaning up model for screenshotting, doing some tests
2026-06-11 hotfire sequence !!!!
2026-06-11 sequence otfv update!
2026-06-11 activate cold flow sequence for servo pressure spik characterization
2026-06-11 fix cold flow indents
2026-06-11 otfv sequence edit
2026-06-11 got mpc_testing working with real lunar landing params
    going to start changing hyperparameter_sweep.ipynb
2026-06-11 switch to hot fire sequence
2026-06-11 cold flow 2 data analysis update + sequence yaml bug fix
2026-06-11 final hotfire seqeunce
2026-06-11 no throttle for first run
2026-06-12 hotfire sequence + data analysis
2026-06-12 open ftvv instead of close
2026-06-12 igniter test data + 0.2 seconds between oifv and fifv
2026-06-12 sparker step changed to manual
